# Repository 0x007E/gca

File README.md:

# `GCA` - Game Card Adapter

The `GCA` is a board with a [AT24CM0X](#additional-information) `EEPROM` or any other compatible `EEPROM`. The board itself can be driven with a voltage from `3V3-5V` and is used chainload games onto the [GamePad](https://github.com/0x007e/gap) over the integrated bootloader (currently under development). 

| Experience  | Level                                                                               |
|:------------|:-----------------------------------------------------------------------------------:|
| Soldering   |  |
| Mechanical  |     |

# Downloads

| Type      | File                                                                                                                                                 | Description     |
|:---------:|:----------------------------------------------------------------------------------------------------------------------------------------------------:|:----------------|
| Schematic | [pdf](https://github.com/0x007E/gca/releases/latest/download/schematic.pdf) / [cadlab](https://cadlab.io/project/30397/main/files)                   | Schematic files |
| Board     | [pdf](https://github.com/0x007E/gca/releases/latest/download/pcb.pdf) / [cadlab](https://cadlab.io/project/30397/main/files)                         | Board file      |
| Drill     | [pdf](https://github.com/0x007E/gca/releases/latest/download/drill.pdf)                                                                              | Drill file      |
| BoM | [xlsx](https://github.com/0x007E/gca/releases/latest/download/bom.xlsx) / [html](https://github.com/0x007E/gca/releases/latest/download/bom.html)          | Bill of Material as Excel/interactive HTML |
| PCB    | [zip](https://github.com/0x007E/gca/releases/latest/download/kicad.zip) / [tar](https://github.com/0x007E/gca/releases/latest/download/kicad.tar.gz)    | KiCAD/Gerber/BoM/Drill files       |
| Mechanical | [zip](https://github.com/0x007E/gca/releases/latest/download/freecad.zip) / [tar](https://github.com/0x007E/gca/releases/latest/download/freecad.tar.gz) | FreeCAD/Housing and PCB (STEP/STL) files     |

# Hardware

The pcb is created with `KiCAD`, the housing with `FreeCAD`. All files are built with `github actions` so that they are ready for a production environment.

## PCB

The circuit board is populated on both sides (Top, Bottom). The best way for soldering the `SMD` components is within a vapor phase soldering system and for the `THT` components with a standard soldering system.

### Top Layer

### Bottom Layer

## Mechanical

The housing has a tolerance of `0.2mm` on each side of the case. So the pcb should fit perfectly in the housing. The tolerance can be modified with `FreeCAD` in the `Parameter` Spreadsheet.

### Assembled

### Exploded

# Additional Information

| Type       | Link               | Description              |
|:----------:|:------------------:|:-------------------------|
| AT24CM02 | [pdf](https://ww1.microchip.com/downloads/en/DeviceDoc/AT24CM02-I2C-Compatible-Two-Wire-Serial-EEPROM-2-Mbit-262,144x8-20006197C.pdf) | 2-MBit serial EEPROM dataseheet |
| AT24CM01 | [pdf](https://ww1.microchip.com/downloads/en/DeviceDoc/AT24CM01-I2C-Compatible-Two-Wire-Serial-EEPROM-Data-Sheet-20006170A.pdf) | 1-MBit serial EEPROM datasheet |

---

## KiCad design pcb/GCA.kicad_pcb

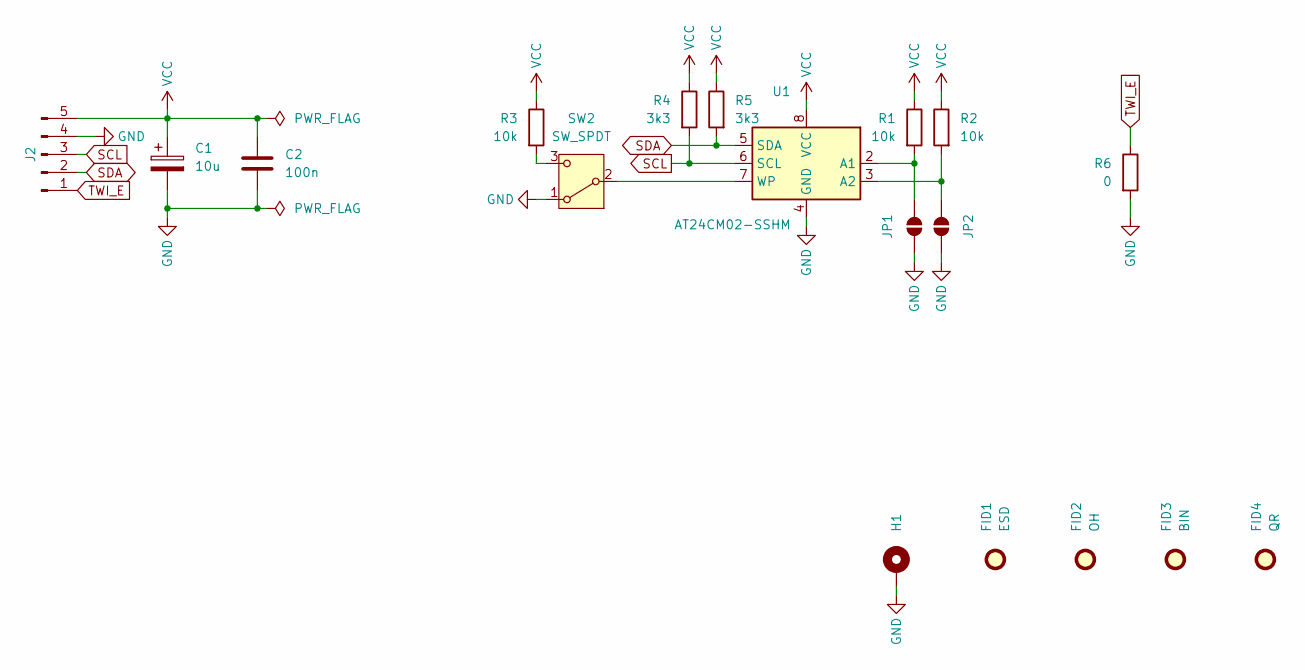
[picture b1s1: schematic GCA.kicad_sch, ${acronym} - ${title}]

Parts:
C1: 10u; CP_EIA-6032-28_Kemet-C
C2: 100n; C_1206_3216Metric
FID1: ESD; ESD-Logo_6.6x6mm_SilkScreen
FID2: OH; OSHW-Logo_5.7x6mm_SilkScreen
FID3: BIN; WEEE-Logo_4.2x6mm_SilkScreen
FID4: QR; QR_0x007e_very_small
H1: MountingHole_Pad; MountingHole_2.7mm_M2.5_DIN965_Pad
J2: Conn_01x05_Pin; PinHeader_1x05_P2.54mm_Horizontal
JP1, JP2: SolderJumper_2_Open; SolderJumper-2_P1.3mm_Open_RoundedPad1.0x1.5mm
R1, R2, R3: 10k; R_1206_3216Metric
R4, R5: 3k3; R_1206_3216Metric
R6: 0; R_1206_3216Metric
SW2: SW_SPDT; SW_SPDT_CK_JS102011SAQN
U1: AT24CM02-SSHM; SOIC-8_3.9x4.9mm_P1.27mm

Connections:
GND: C1.2, C2.2, H1.1, J2.4, JP1.1 (A), JP2.1 (A), R6.2, SW2.1 (A), U1.4 (GND)
unnamed: JP1.2 (B), R1.2, U1.2 (A1)
unnamed: JP2.2 (B), R2.2, U1.3 (A2)
unnamed: SW2.2 (B), U1.7 (WP)
unnamed: R3.2, SW2.3 (C)
SCL: J2.3, R4.2, U1.6 (SCL)
SDA: J2.2, R5.2, U1.5 (SDA)
TWI_E: J2.1, R6.1
VCC: C1.1, C2.1, J2.5, R1.1, R2.1, R3.1, R4.1, R5.1, U1.8 (VCC)

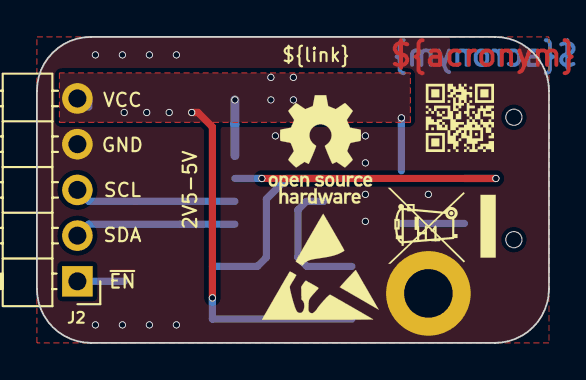
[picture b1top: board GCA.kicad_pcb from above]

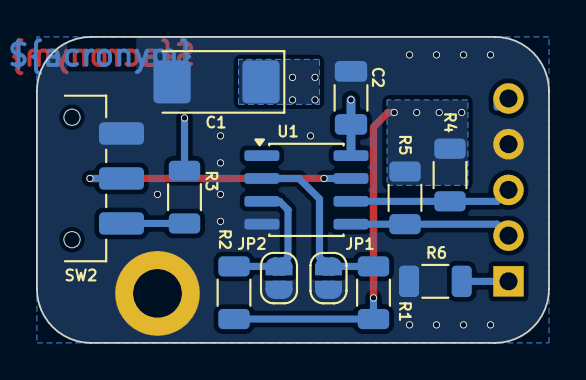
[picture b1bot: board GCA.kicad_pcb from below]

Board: 2 copper layers, 28.4 x 17.0 mm, 18 parts (12 on the bottom side), 9 nets.

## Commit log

2026-03-11 Add pcb layout
2026-04-08 Flip connector to top
2026-05-31 Optimize circuit position
2026-05-31 Fix fabrication layer view
2026-05-31 Rename/Add/Remove bom fields
2026-05-31 Add dimensioning
2026-06-01 Add mechanical parts
2026-06-01 Add build pipeline
2026-06-01 Add release pipeline
2026-06-01 Add assembly explosion
2026-06-01 Add README.md
2026-06-01 Optimize mechanical design

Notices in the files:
README.md:
License CC By-NC-SA
parts and their libraries:
license: CC BY-NC-SA 4.0
